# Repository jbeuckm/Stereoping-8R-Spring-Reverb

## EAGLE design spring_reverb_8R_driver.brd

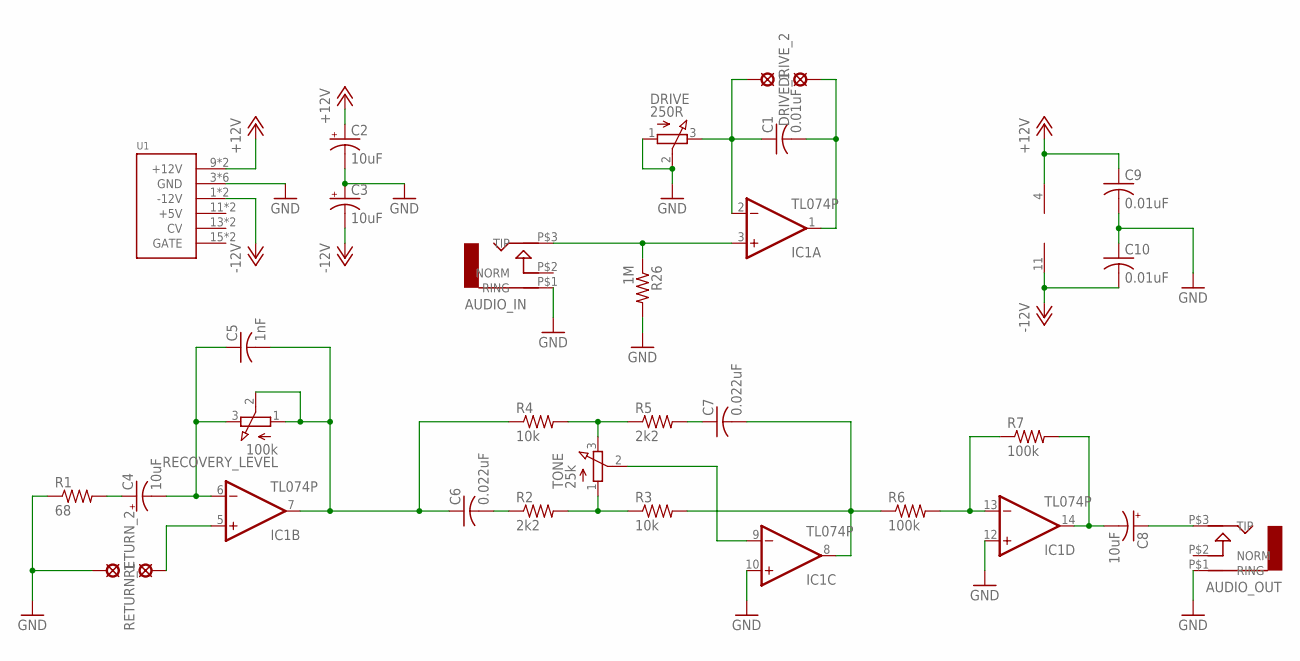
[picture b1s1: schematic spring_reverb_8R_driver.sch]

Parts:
AUDIO_IN: AUDIO-JACK; ERTHENVAR-JACK-90DEG
AUDIO_OUT: AUDIO-JACK; ERTHENVAR-JACK-90DEG
C1, C9, C10: 0.01uF; C050-024X044
C2, C3, C4, C8: 10uF; B45181A
C5: 1nF; C050-024X044
C6, C7: 0.022uF; C050-024X044
DRIVE: 250R; 3RP/1610N
DRIVE_1, DRIVE_2: LSP11
IC1: TL074P; DIL14
R1: 68; 0207/7
R2, R5: 2k2; 0207/7
R3, R4: 10k; 0207/7
R6, R7: 100k; 0207/7
R26: 1M; 0207/7
RECOVERY_LEVEL: 100k; 3RP/1610N
RETURN_1, RETURN_2: LSP11
TONE: 25k; 3RP/1610N
U1: POWER; POWER_16

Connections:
+12V: C2.+, C9.1, IC1.4 (V+), U1.9 (+12V), U1.10 (+12V)
-12V: C3.-, C10.2, IC1.11 (V-), U1.1 (-12V), U1.2 (-12V)
GND: AUDIO_IN.P$1 (RING), AUDIO_OUT.P$1 (RING), C2.-, C3.+, C9.2, C10.1, DRIVE.1 (A), DRIVE.2 (S), IC1.10 (+IN), IC1.12 (+IN), R1.1, R26.2, RETURN_1.MP, U1.3 (GND), U1.4 (GND), U1.5 (GND), U1.6 (GND), U1.7 (GND), U1.8 (GND)
unnamed: C1.2, DRIVE_2.MP, IC1.1 (OUT)
unnamed: C1.1, DRIVE.3 (E), DRIVE_1.MP, IC1.2 (-IN)
unnamed: C4.+, R1.2
unnamed: C4.-, C5.1, IC1.6 (-IN), RECOVERY_LEVEL.3 (E)
unnamed: IC1.5 (+IN), RETURN_2.MP
unnamed: C5.2, C6.1, IC1.7 (OUT), R4.1, RECOVERY_LEVEL.1 (A), RECOVERY_LEVEL.2 (S)
unnamed: C6.2, R2.1
unnamed: C7.1, R5.2
unnamed: R2.2, R3.1, TONE.1 (A)
unnamed: R4.2, R5.1, TONE.3 (E)
unnamed: C7.2, IC1.8 (OUT), R3.2, R6.1
unnamed: IC1.9 (-IN), TONE.2 (S)
unnamed: AUDIO_OUT.P$3 (TIP), C8.+
unnamed: C8.-, IC1.14 (OUT), R7.2
unnamed: IC1.13 (-IN), R6.2, R7.1
unnamed: AUDIO_IN.P$3 (TIP), IC1.3 (+IN), R26.1

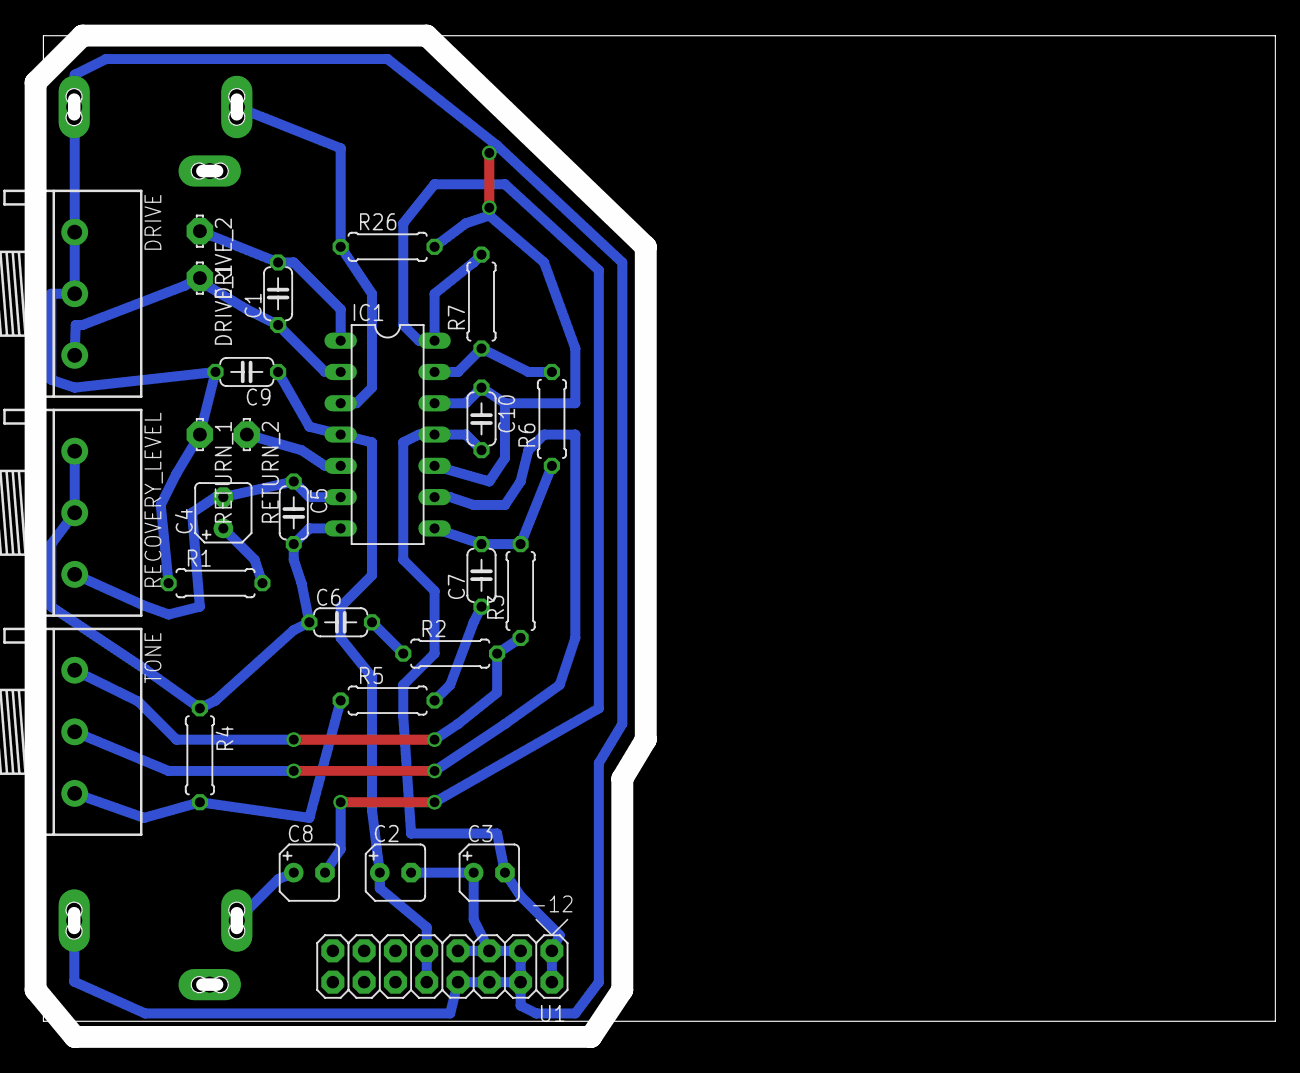
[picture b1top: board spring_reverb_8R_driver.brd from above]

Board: 2 copper layers, 99.7 x 81.3 mm, 29 parts (0 on the bottom side), 19 nets.

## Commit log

2016-01-05 panel
2016-01-18 corrected pot directions and slimmer layout
